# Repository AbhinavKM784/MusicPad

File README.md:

# MusicPad
Designing a music pad 4 keys and volume knob

Schematic

PCB

How my 3d printed parts fit together before all the components

Coding

how my all my parts will look after fitted and soldered

BOM:
Seeed XIAO RP2040
Through-hole 1N4148 Diodes (Max 20x)
MX-Style switches (Max 16x)
EC11 Rotary encoders (Max 2x)
Blank DSA keycaps (White)
SK6812 MINI-E LEDs (Max 16x)
M3x16mm screws
M3x5mx4mm heatset inserts
3D PRINTED CASE ONLY. NO ACRYLIC.

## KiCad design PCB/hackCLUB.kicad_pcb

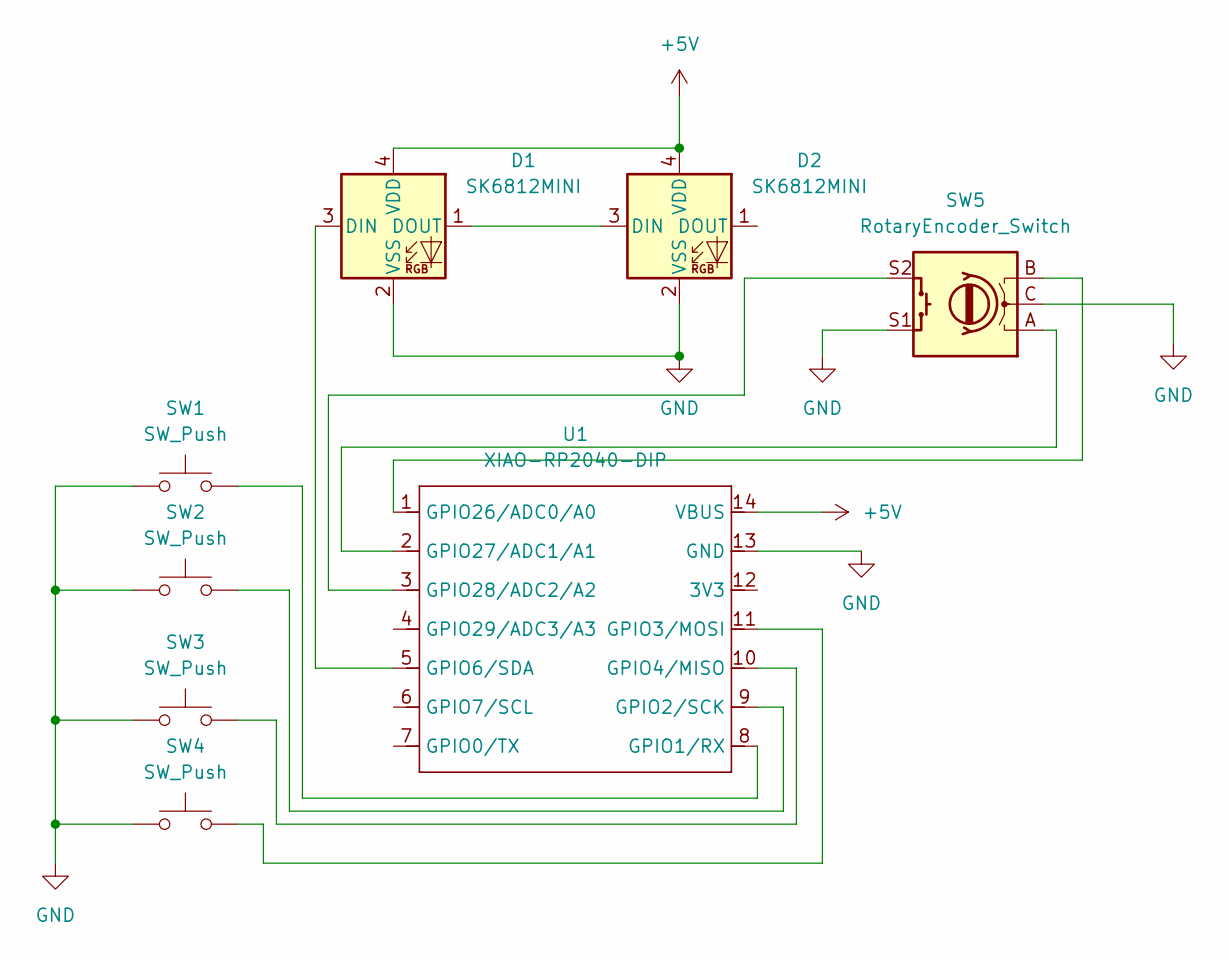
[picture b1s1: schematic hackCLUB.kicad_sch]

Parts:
D1, D2: SK6812MINI; SK6812MINI-E_fixed
SW1, SW2, SW3, SW4: SW_Push; SW_Cherry_MX_1.00u_PCB
SW5: RotaryEncoder_Switch; RotaryEncoder_Alps_EC11E-Switch_Vertical_H20mm_CircularMoun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
U1: XIAO-RP2040-DIP

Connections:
+5V: D1.4 (VDD), D2.4 (VDD), U1.14 (VBUS)
GND: D1.2 (VSS), D2.2 (VSS), SW1.1, SW2.1, SW3.1, SW4.1, SW5.C, SW5.S1, U1.13 (GND)
unnamed: D1.3 (DIN), U1.5 (GPIO6/SDA)
unnamed: D1.1 (DOUT), D2.3 (DIN)
unnamed: SW1.2, U1.8 (GPIO1/RX)
unnamed: SW2.2, U1.9 (GPIO2/SCK)
unnamed: SW4.2, U1.11 (GPIO3/MOSI)
unnamed: SW3.2, U1.10 (GPIO4/MISO)
unnamed: SW5.B, U1.1 (GPIO26/ADC0/A0)
unnamed: SW5.A, U1.2 (GPIO27/ADC1/A1)
unnamed: SW5.S2, U1.3 (GPIO28/ADC2/A2)

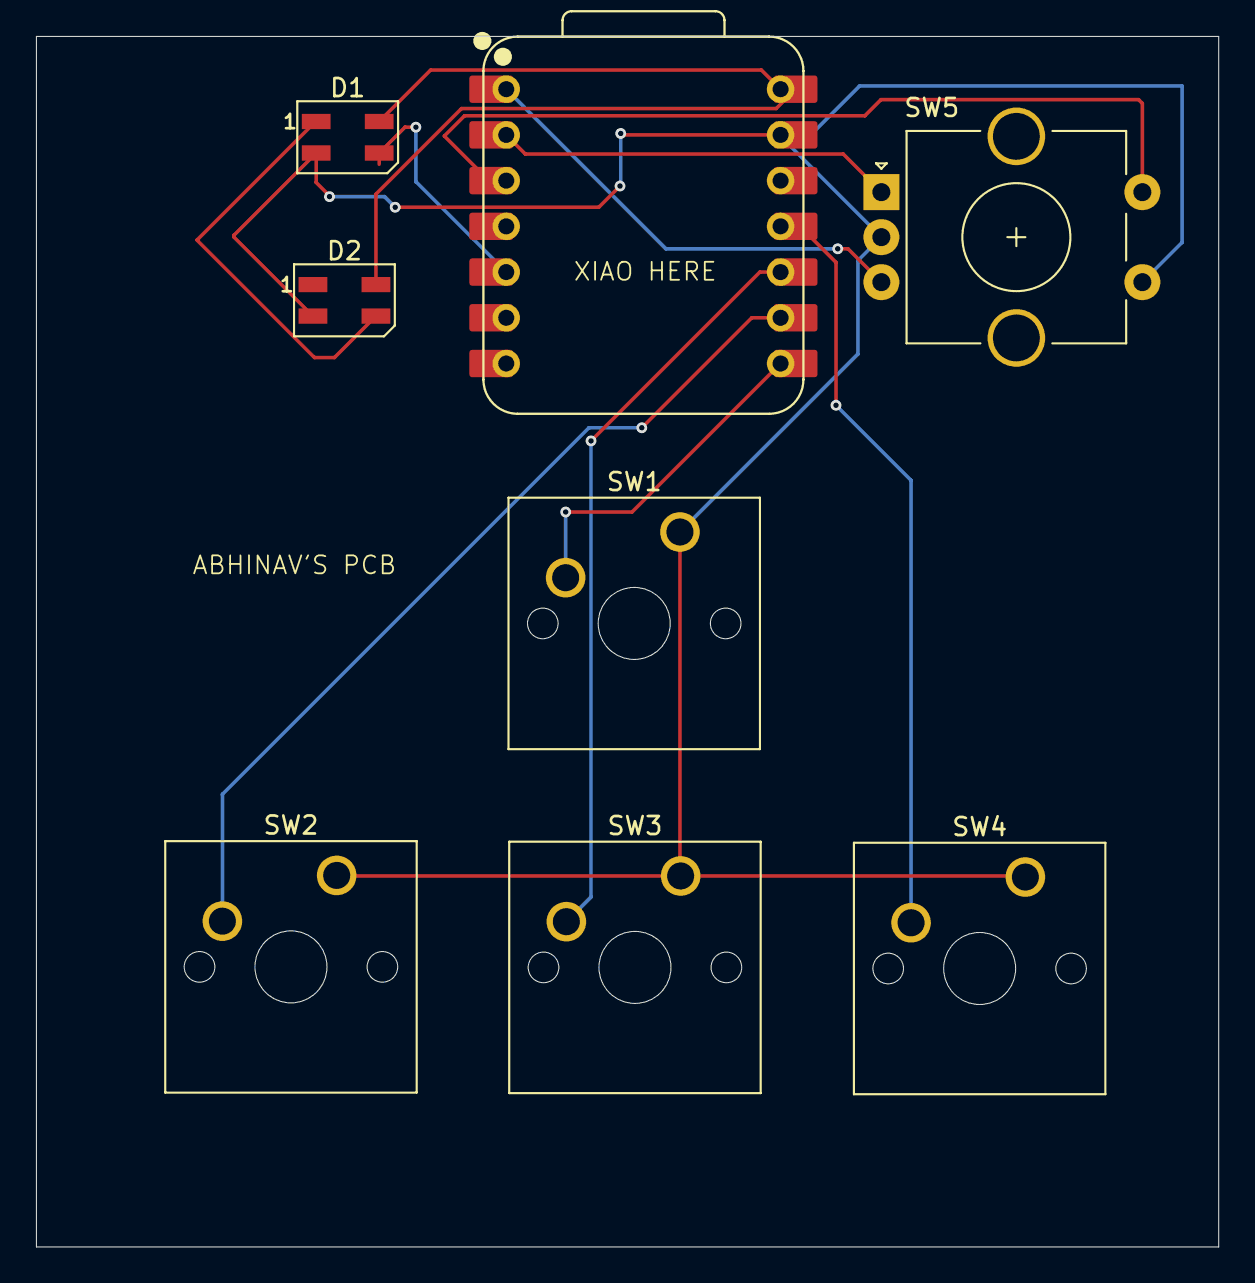
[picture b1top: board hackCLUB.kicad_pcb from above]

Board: 2 copper layers, 65.7 x 67.2 mm, 8 parts (0 on the bottom side), 11 nets.

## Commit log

2025-12-28 Add README
2026-01-05 Changing the PCB
